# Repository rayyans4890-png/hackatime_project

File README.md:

# My Hackpad

This is a custom Hackpad I made for Hack Club Stardance.

I designed the PCB, made a case for it, and added firmware so all of the switches can be programmed to do different things.

## Features

* 5 switches
* Custom PCB
* Custom firmware
* USB connection

## Pictures

### Final Hackpad

### PCB

### Case

### PCB Schematic

## BOM

| Part             |     Quantity |
| ---------------- | -----------: |
| Seeed XIAO       |            1 |
| Switches         |            5 |
| Keycaps          |            5 |
| Custom PCB       |            1 |
| Case             |            1 |

## Tools Used

* KiCad
* Fusion 360
* QMK Firmware 

## Firmware

The firmware is included in this repository. It is used to make the switches work and can be changed to give the buttons different functions.

The compiled firmware is also in the `production` folder.

## Files

The `production` folder contains the files needed to make the Hackpad:

* `gerbers.zip` - PCB manufacturing files
* Case files
* Compiled firmware

The rest of the repository contains the PCB, case, and firmware source files.

## Testing

I tested the finished Hackpad to make sure all 5 switches register correctly and that the PCB, firmware, and case all work together.

## Made For

Hack Club Stardance

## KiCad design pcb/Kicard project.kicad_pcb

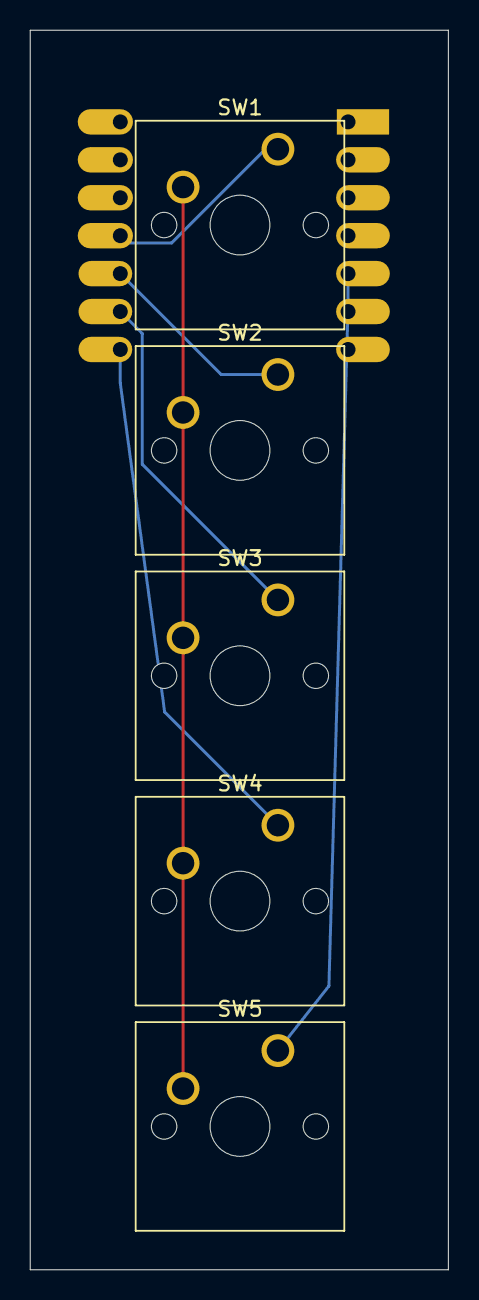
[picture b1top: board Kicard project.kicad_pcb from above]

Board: 2 copper layers, 28.0 x 83.0 mm, 6 parts (1 on the bottom side), 6 nets.

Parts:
SW1, SW2, SW3, SW4, SW5: SW_Push; SW_Cherry_MX_1.00u_PCB
U1: MOUDLE-SEEEDUINO-XIAO; XIAO-Generic-Hybrid-14P-2.54-21X17.8MM

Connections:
GND: SW1.2, SW2.2, SW3.2, SW4.2, SW5.2, U1.13 (GND)
unnamed: SW2.1, U1.10 (PA5_A9_D9_MISO)
unnamed: SW1.1, U1.11 (PA6_A10_D10_MOSI)
unnamed: SW3.1, U1.9 (PA7_A8_D8_SCK)
unnamed: SW5.1, U1.5 (PA8_A4_D4_SDA)
unnamed: SW4.1, U1.8 (PB09_A7_D7_RX)
